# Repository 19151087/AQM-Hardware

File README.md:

++++++++++++++ AIR QUALITY MONITOR PCB DESIGN ++++++++++++

ESP32 WROOM 32

USB Type C for power supply
LCD TFT 3.2' HSPI communication
PMS7003 sensor UART communication
SHT31 sensor I2C communication
DS3231 RTC I2C communication
microSD card VSPI communication

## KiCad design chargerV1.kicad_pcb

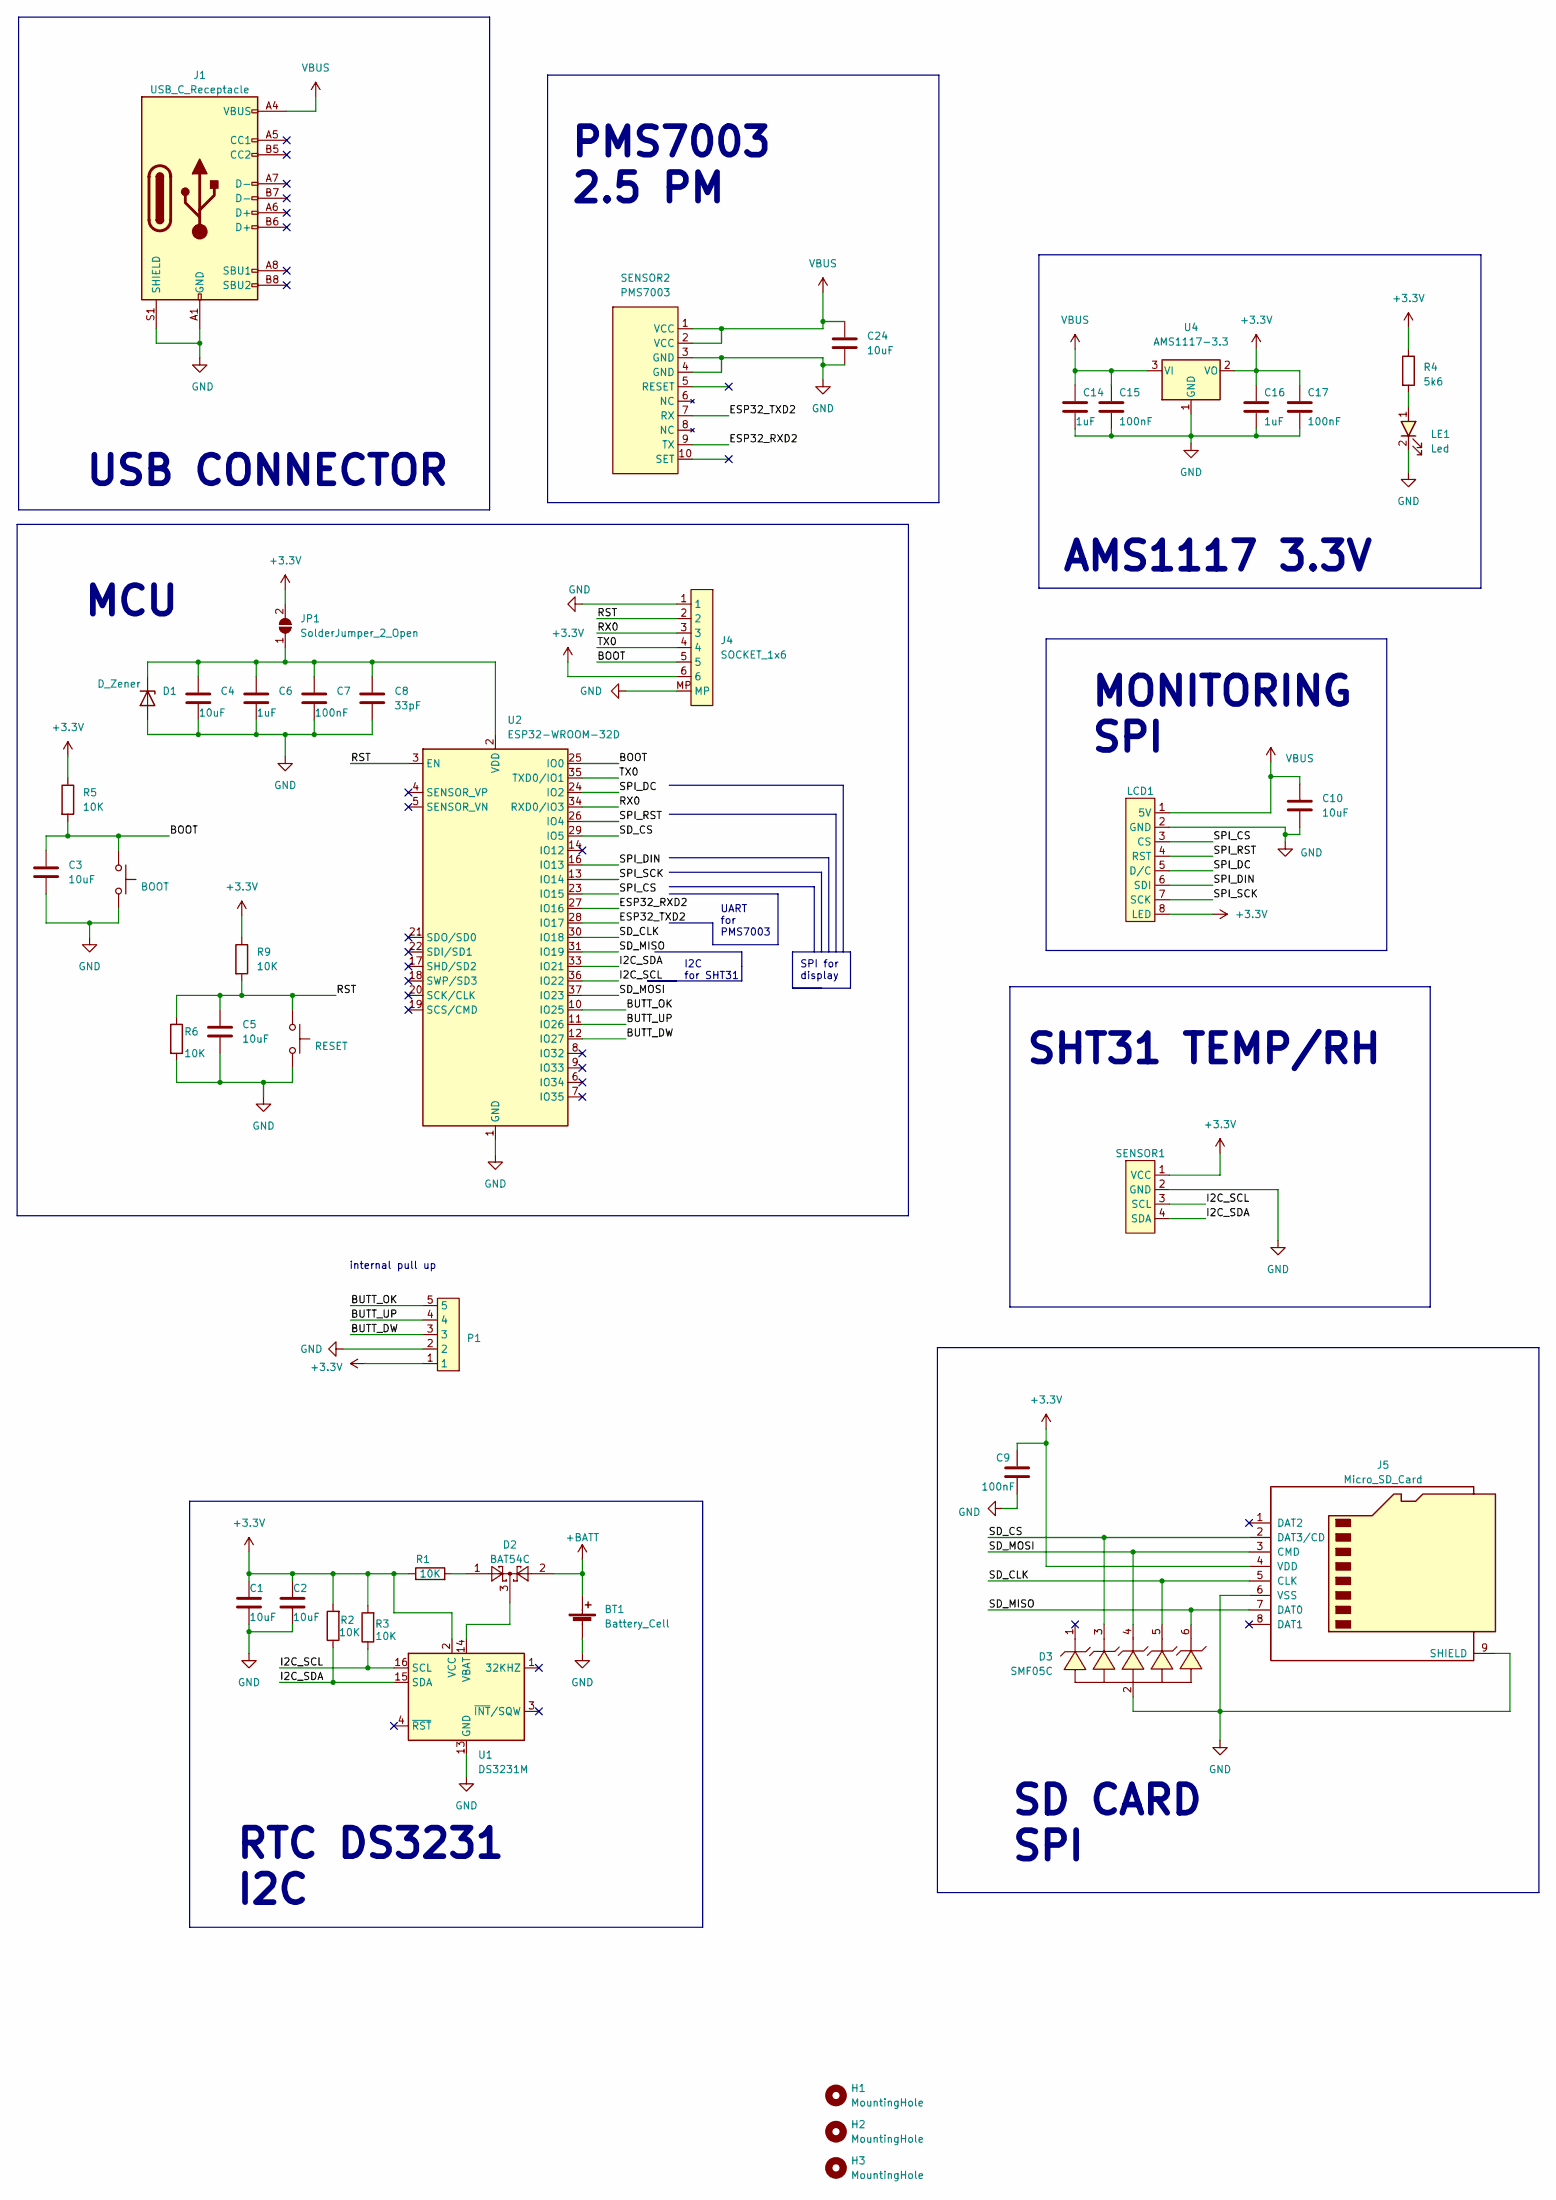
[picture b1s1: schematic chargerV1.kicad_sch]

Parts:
BT1: Battery_Cell; BatteryHolder_CR1220
C1, C2, C3, C4, C5, C10, C24: 10uF; C_0603
C6, C14, C16: 1uF; C_0603
C7, C9, C15, C17: 100nF; C_0603
C8: 33pF; C_0603
D1: D_Zener; D_MiniMELF
D2: BAT54C; SOT-23
D3: SMF05C; TSSOP-6
H1, H2, H3: MountingHole; MountingHole_2.2mm_M2_Pad_Via
J1: USB_C_Receptacle; USB_C_Receptacle_XKB_U262-16XN-4BVC11
J4: SOCKET_1x6; JST_SH_SM06B-SRSS-TB_1x06-1MP_P1.00mm_Horizontal
J5: Micro_SD_Card; MicroSD_Socket_9P
JP1: SolderJumper_2_Open; SolderJumper-2_P1.3mm_Open_Pad1.0x1.5mm
LCD1: JST_SH_SM08B-SRSS-TB_1x08-1MP_P1.00mm_Horizontal
LE1: Led; LED0603
P1: JST_SH_SM05B-SRSS-TB_1x05-1MP_P1.00mm_Horizontal
R1, R2, R3, R5, R6, R9: 10K; R0603
R4: 5k6; R0603
SENSOR1: JST_SH_SM04B-SRSS-TB_1x04-1MP_P1.00mm_Horizontal
SENSOR2: PMS7003
SW1: BOOT; SW_SPST_PTS810
SW3: RESET; SW_SPST_PTS810
U1: DS3231M; SOIC-16W_7.5x10.3mm_P1.27mm
U2: ESP32-WROOM-32D; ESP32-WROOM-32
U4: AMS1117-3.3; SOT-223-3_TabPin2

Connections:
+3.3V: C1.1, C2.1, C9.1, C16.1, C17.1, J4.6, J5.4 (VDD), JP1.2 (B), LCD1.8 (LED), P1.1, R1.1, R2.2, R3.2, R4.1, R5.1, R9.1, SENSOR1.1 (VCC), U1.2 (VCC), U4.2 (VO)
+BATT: BT1.1 (+), D2.2
/BOOT: C3.1, J4.5, R5.2, SW1.1, U2.25 (IO0)
/BUTT_DW: P1.3, U2.12 (IO27)
/BUTT_OK: P1.5, U2.10 (IO25)
/BUTT_UP: P1.4, U2.11 (IO26)
/ESP32_RXD2: SENSOR2.9 (TX), U2.27 (IO16)
/ESP32_TXD2: SENSOR2.7 (RX), U2.28 (IO17)
/I2C_SCL: R3.1, SENSOR1.3 (SCL), U1.16 (SCL), U2.36 (IO22)
/I2C_SDA: R2.1, SENSOR1.4 (SDA), U1.15 (SDA), U2.33 (IO21)
/RST: C5.1, J4.2, R6.1, R9.2, SW3.1, U2.3 (EN)
/RX0: J4.3, U2.34 (RXD0/IO3)
/SD_CLK: D3.5, J5.5 (CLK), U2.30 (IO18)
/SD_CS: D3.3, J5.2 (DAT3/CD), U2.29 (IO5)
/SD_MISO: D3.6, J5.7 (DAT0), U2.31 (IO19)
/SD_MOSI: D3.4, J5.3 (CMD), U2.37 (IO23)
/SPI_CS: LCD1.3 (CS), U2.23 (IO15)
/SPI_DC: LCD1.5 (D/C), U2.24 (IO2)
/SPI_DIN: LCD1.6 (SDI), U2.16 (IO13)
/SPI_RST: LCD1.4 (RST), U2.26 (IO4)
/SPI_SCK: LCD1.7 (SCK), U2.13 (IO14)
/TX0: J4.4, U2.35 (TXD0/IO1)
GND: BT1.2 (-), C1.2, C2.2, C3.2, C4.2, C5.2, C6.2, C7.2, C8.2, C9.2, C10.2, C14.2, C15.2, C16.2, C17.2, C24.2, D1.2 (A), D3.2, J1.A1 (GND), J1.A12 (GND), J1.B1 (GND), J1.B12 (GND), J1.S1 (SHIELD), J4.1, J4.MP, J5.6 (VSS), J5.9 (SHIELD), LCD1.2 (GND), LE1.2, P1.2, R6.2, SENSOR1.2 (GND), SENSOR1.MP, SENSOR2.3 (GND), SENSOR2.4 (GND), SW1.2, SW3.2, U1.5 (GND), U1.6 (GND), U1.7 (GND), U1.8 (GND), U1.9 (GND), U1.10 (GND), U1.11 (GND), U1.12 (GND), U1.13 (GND), U2.1 (GND), U2.15 (GND), U2.38 (GND), U2.39 (GND), U4.1 (GND)
unnamed: C4.1, C6.1, C7.1, C8.1, D1.1 (K), JP1.1 (A), U2.2 (VDD)
unnamed: D2.1, R1.2
unnamed: LE1.1, R4.2
unnamed: D2.3, U1.14 (VBAT)
VBUS: C10.1, C14.1, C15.1, C24.1, J1.A4 (VBUS), J1.A9 (VBUS), J1.B4 (VBUS), J1.B9 (VBUS), LCD1.1 (5V), SENSOR2.1 (VCC), SENSOR2.2 (VCC), U4.3 (VI)

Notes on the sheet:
internal pull up
PMS7003 2.5 PM
SD CARD SPI
UART for PMS7003
SHT31 TEMP/RH
I2C for SHT31
AMS1117 3.3V
USB CONNECTOR
SPI for display
RTC DS3231 I2C
MONITORING SPI
MCU

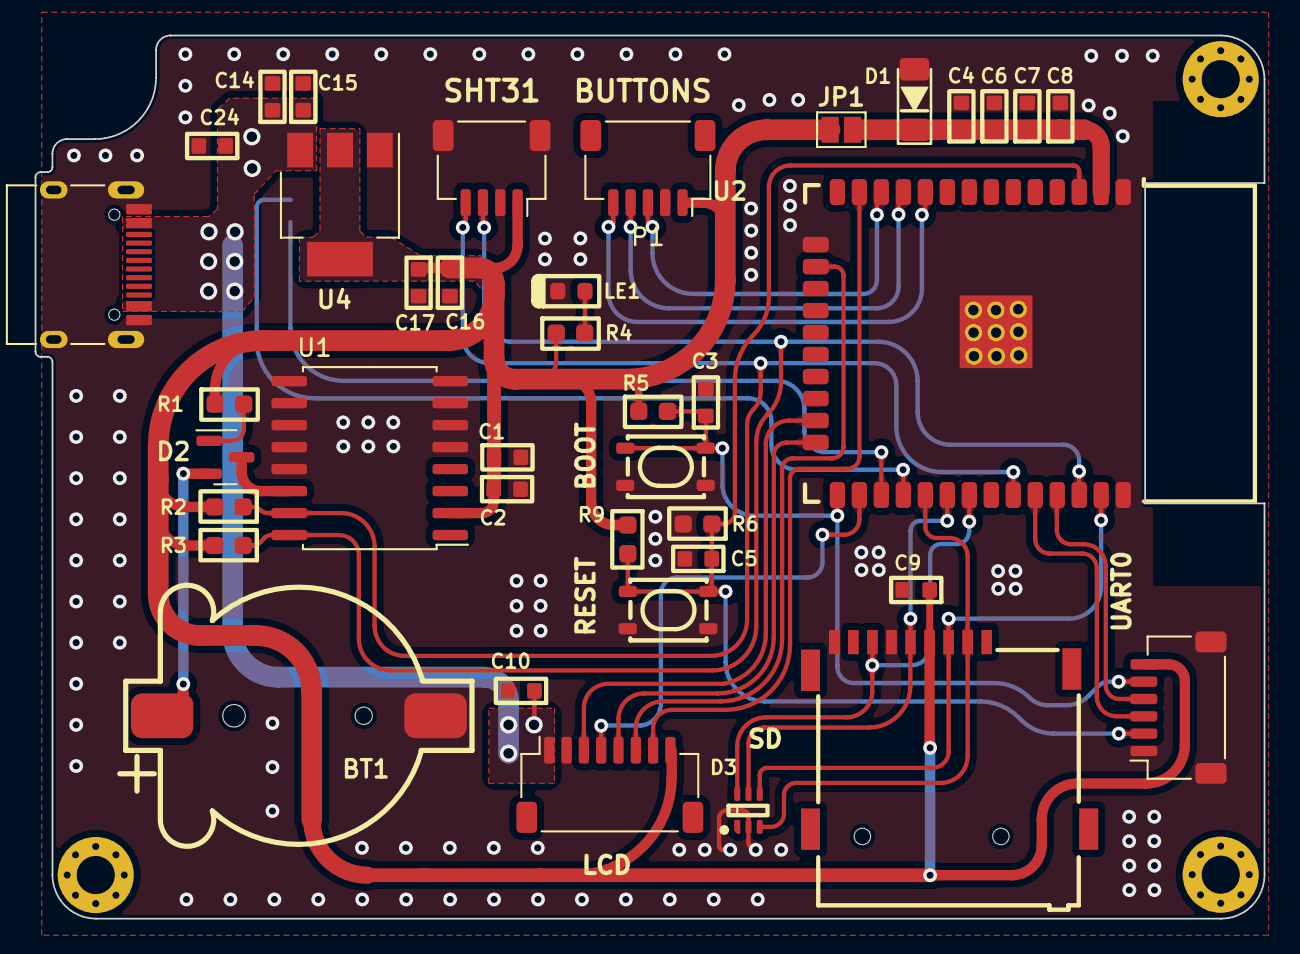
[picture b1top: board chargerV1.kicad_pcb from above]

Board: 2 copper layers, 71.0 x 51.0 mm, 43 parts (1 on the bottom side), 28 nets.

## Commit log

2023-04-14 First commit message
2023-04-14 Add README.md
2023-04-14 Add modifies
2023-04-14 Add more modifies
2023-05-16 Fix buttons
2023-05-20 fix usb

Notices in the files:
parts and their libraries:
Copyright 2021 Accelerated Designs. All rights reserved.
